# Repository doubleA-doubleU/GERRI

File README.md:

## GERRI (Guidance Enabled Robotic Raceline Interpreter)
#### _Aaron Weatherly_
#### _Northwestern University_

<p>
<br>

<br>
</p>

## Overview
This project allows an off-the-shelf radio controlled car to be converted
into an autonomous vehicle. This is accomplished by replacing the car's 
control system with an Android phone and a PIC32 microcontroller. External
localization is done through HTC vive position sensors. Check out this 
[video][youtube] for a demonstration.

## Required Components 
1. Android phone (I used a Samsung Galaxy S5)
2. Radio Controlled Car (I used a Tamiya TL01)
3. USB OTG cable - micro to mini
4. 3D printed [phone and PCB mounts][parts]
5. Microchip [PIC32MX250F128B][pic] microcontroller in 28-pin SPDIP package
6. VNH5019 [Motor Driver Carrier][hbridge]
7. HTC Vive [Base Station][base]
8. 2x HTC Vive Position Sensor, [TS3633-CM1][vive]
9. Custom [PCB][pcb] with mounting holes for:
	* 28 Pin DIP socket
	* Mini USB connector
	* Slideswitch
	* MCP1702 voltage regulator (TO92)
	* 3mm red LED with 330 Ohm resistor
	* Reset button with 10 kOhm resistor
	* 3mm green LED with 330 Ohm resistor
	* User button with 10 kOhm resistor
	* 8 MHz crystal resonator
	* 4x 0.1 uF capacitors
	* 2x 10 uF polarized capacitors
	* 5-pin breakout for PICkit3 programmer
	* 2x 8-pin breakouts for remaining I/O pins and power/ground connections

## Software
#### In MPLAB X IDE:
1. Create new 32-bit MPLAB Harmony project, named GERRI, for the PIC32MX250F128B
2. Generate code
3. Copy all code from the provided [app.c][appc], [app.h][apph], 
[main.c][main], [default.mhc][default], [system_config.h][config], 
and [system_interrupt.c][interrupt]	into the auto-generated Harmony 
files of same names
4. Install the project onto the PIC
	
#### In Android Studio:
1. Create new project with an Empty Activity, named GERRI
2. Copy the provided [classes.jar][classes] to <your_local_project_path>/GERRI/app/libs/
3. In the IDE, navigate the left panel to Project/GERRI/app/libs/
4. Right click classes.jar, Add as Library, Add to Module: app
5. In the IDE, navigate the left panel to Android/app/res/
6. Right click res, add driectory, name it "xml"
7. Right click xml, add new XML Resource file, name it "device_filter.xml"
8. Open this new xml file and replace the contents with the code from 
the provided [device_filter.xml][filter] file
9. Copy all code from the provided [activity_main.xml][layout], 
[AndroidManifest.xml][manifest], and [MainActivity.java][java] into 
the auto-generated Android Studio files of same name.

## Under the Hood
This is an extension of a much simpler line-following [robot][pathfinder].

#### The Android app:
GERRI begins by using the phone's camera to identify the track ahead. For
me, the track was designated by blue painter's tape, so the key 
lines from `MainActivity.java` are:
```java
for (int startY = 180; startY <= 300; startY = startY + 20) { // which row in the bitmap to analyze to read
    bmp.getPixels(pixels, 0, bmp.getWidth(), 0, startY, bmp.getWidth(), 1);
    // in the row, see if the pixel is blue
    for (int i = 0; i < bmp.getWidth(); i++) {
        if (blue(pixels[i]) > thresh) {
            pixels[i] = rgb(0, 255, 0); // over write the pixel with pure green
            // COM pixel calculation
            M = M + 1;
            sum = sum + i;
        }
    }
    // update the row
    bmp.setPixels(pixels, 0, bmp.getWidth(), 0, startY, bmp.getWidth(), 1);

    // calculate COM for each row
    if (M == 0) {
        COM = 0;
    } else {
        COM = (sum / M) + 1;
        COMavg += COM;
        count++;
    }
}
```
This loop occurs each time there is a new camera frame. We analyze several
rows of pixels, identify which ones are blue, then calculate the average
position for the portion of the track that can be seen. Then, the following
uses a fixed transform from the camera frame to the world frame to determine
where the track is and add that point to a bitmap representing the track:
```java
// average the COMs
if (count == 0) {
    COMavg = 0;
} else {
    COMavg = COMavg / count;
    // calculate a point on the track based on COMavg, xCar, yCar, theta
    float l = (float) (0.025*COMavg); // distance from left of frame to the COM (in cm)
    float d = (float) (Math.sqrt(Math.pow(18.2,2) - Math.pow(l,2))); // distance from the car to the COM (in cm)
    float theta2 = (float) (Math.atan2(8-l,16.35)); // angle from the car to the COM along a line 16.35 cm from car's position (in radians)
    xTrack = (int) (xCar*100 + d*Math.cos(theta + theta2) + 0.5);
    yTrack = (int) (yCar*100 - 200 + d*Math.sin(theta + theta2) +0.5);
    if (lapTime<0.1) {
        xInit = xTrack;
        yInit = yTrack;
    }
    // add that point to the track bitmap
    if (c2 != null) {
		try {
			bmp2.setPixel(xTrack, yTrack, 0xffffffff);
		} catch (Exception e) {}
    }
}
// draw circle at COM
canvas.drawCircle(COMavg, 240, 5, paint1);
// write the COM as text
canvas.drawText("COM = " + COMavg, 10, 30, paint1);
//send COM to PIC
String sendString = String.valueOf(COMavg) + '\n';
try {
    sPort.write(sendString.getBytes(), 1); // 1 is the timeout
} catch (IOException e) {}
```
This process continues until GERRI has completed its first lap and generated
a map of the entire track. It then switches modes from simple line-following 
to a proportional feedback controller that uses the track bitmap as the desired
path. The first step in this phase is to find the nearest point on the track
from the car's current position:
```java
// find nearest white pixel in bmp2 by looking at the rings of pixels around current location
int x = (int) (xCar*100 + 0.5); // convert to cm
int y = (int) (yCar*100 - 200 + 0.5); // convert to cm, shift to fit the bitmap's range
outerLoop:
for (int ring=0; ring<15;ring++) { // looking within 15cm radius
    int[] pixels = new int[2*ring+1];
    for (int row = -ring; row <= ring; row++) {
        try {
            bmp2.getPixels(pixels,0,bmp2.getWidth(),x-ring,y+row,2*ring+1,1);
        } catch (IllegalArgumentException iae) {} // sometimes the data is bad...
        for (int col = -ring; col <= ring; col++) {
            if (pixels[col+ring] == 0xffffffff) {
                // if the pixel is white, define (xDesired,yDesired) as the current row and column of the search
                xDesired = x+col;
                yDesired = y+row;
                if (xDesired_prev == 0) {
                    xDesired_prev = xDesired;
                    yDesired_prev = yDesired;
                }
                // break the both for loops once the track is found
                break outerLoop;
            }
        }
    }
}
```
Next, we calculate the position and angular error as follows:
```java
// calculate position error
posError = (float) Math.sqrt(Math.pow(xDesired - x,2) + Math.pow(yDesired - y,2));

if (posError != 0 && xDesired - xDesired_prev != 0) {
	// calculate desired angle based on current vs previous track points
    thetaDesired = (float) Math.atan2(yDesired - yDesired_prev, xDesired - xDesired_prev);
    if (Math.abs(thetaDesired-thetaDesired_prev) > 0.5) {
        thetaDesired = thetaDesired_prev;
    }
    // calculate angular error
    angError = thetaDesired - theta;
} else {
    if (thetaDesired_prev == 0){
        thetaDesired = theta;
        angError = 0;
    }
    else {
        thetaDesired = thetaDesired_prev;
        angError = thetaDesired - theta;
    }
}
```
Now we have to determine whether the position error should be positive or
negative by determining whether the track is to the left or right of the
car. There is a hard coded assumption here that the track direction is 
always counterclockwise. This was to simplify the if statements below:
```java
// determine whether track is to the left or right (assuming counterclockwise track direction...)
float theta2 = (float) Math.atan2(yDesired - y, xDesired - x); // angle from car to the track
if (thetaDesired >= Math.PI/2 && thetaDesired < Math.PI) {
    if (theta2 >= Math.PI && theta2 < 3*Math.PI/2) { // the track is to the left of the car
        posError = (-1)*posError;
    }
}
else if (thetaDesired >= Math.PI && thetaDesired < 3*Math.PI/2) {
	if (theta2 >= -Math.PI/2 && theta2 < 0) { // the track is to the left of the car
        posError = (-1)*posError;
    }
}
else if (thetaDesired >= -Math.PI/2 && thetaDesired < 0) {
    if (theta2 >=0 && theta2 < Math.PI/2) { // the track is to the left of the car
        posError = (-1)*posError;
    }
}
else if (thetaDesired >= 0 && thetaDesired < Math.PI/2) {
    if (theta2 >= Math.PI/2 && theta2 < Math.PI) { // the track is to the left of the car
        posError = (-1)*posError;
	}
}
```
Finally, we apply the proportional controller based on the [Stanley method][stanley]
from Stanford's entry into the DARPA Grand Challenge.
```java
// use proportional control to calculate a steering angle value between 0 and 640 based on angError (rad) and posError (cm)
// using the Stanley method: http://robots.stanford.edu/papers/thrun.stanley05.pdf
float cmdRad = angError + (float) Math.atan(thresh2*posError/500); // assuming constant velocity, thresh2 is the proportional gain
float cmdDeg = cmdRad*180/((float) Math.PI);
int cmd;
if (cmdDeg <= -30) {
    cmd = 640;
} else if (cmdDeg >= 30) {
	cmd = 1;
} else {
    cmd = (int) (-320*cmdDeg/30 + 320.5);
}
// send steering command to PIC
String sendString = String.valueOf(cmd) + '\n';
try {
    sPort.write(sendString.getBytes(), 1); // 1 is the timeout
} catch (IOException e) {}
```
In both the mapping and controlled cases, the output of the Android app 
is an integer between 0 and 640 that is proportional to desired steering 
angles between positive and negative 30 degrees that is sent to the PIC.

#### The PIC32 firmware:
The PIC32 communicates with the Android app via USB. It takes the integer value
provided by the app and controlls the motor speed/direction and the servo steering 
angle as shown below (from `app.c`):
```c
if (gotRx) { // rxVal should be an int between 0 and 640 (setting motor speed and steering angle from Center of Mass)
    if (rxVal > 640) {          // stop button pressed, no movement, center the steering, reset lap time
        duty = 0;
        LATAbits.LATA1 = 0;
        LATBbits.LATB2 = 1;
        OC3RS = 1000;
        go = 0;
        lapTime = 0.0;
    } else if (rxVal <= 0) {    // reverse direction and previous steering command to find the line again
        duty = 20;
        LATAbits.LATA1 = 1;     // reverse drive motion
        LATBbits.LATB2 = 0;     // reverse drive motion
        rxVal = rxValPrev;
        OC3RS = 680 + rxValPrev;
        go = 1;
    } else {                    // steer towards the COM
        duty = 20;
        LATAbits.LATA1 = 0;     // forward drive motion
        LATBbits.LATB2 = 1;     // forward drive motion
        OC3RS = 1320 - rxVal;   // ranges from 680 to 1320
        go = 1;
    }
	OC1RS = duty*40;            // convert duty cycle based on period register

    rxPos = 0;
    gotRx = 0; // clear the flag
    rxValPrev = rxVal;
    for (j = 0; j < 64; j++) {
        rx[j] = 0; // clear the array
    }
}
```
The PIC32 also provides the position (x,y,theta) as well as the current lap time to the
Android app via USB (also from `app.c`):
```c
// calculate position
x_pos[0] = (LIGHTHOUSEHEIGHT*sin((x_ang[0])*DEG_TO_RAD))/(sin((60+LIGHTHOUSEANGLE-x_ang[0])*DEG_TO_RAD)*sin((120-LIGHTHOUSEANGLE)*DEG_TO_RAD));
y_pos[0] = (2*LIGHTHOUSEHEIGHT*sin(y_ang[0]*DEG_TO_RAD))/sin((150-y_ang[0])*DEG_TO_RAD);
x_pos[1] = (LIGHTHOUSEHEIGHT*sin((x_ang[1])*DEG_TO_RAD))/(sin((60+LIGHTHOUSEANGLE-x_ang[1])*DEG_TO_RAD)*sin((120-LIGHTHOUSEANGLE)*DEG_TO_RAD));
y_pos[1] = (2*LIGHTHOUSEHEIGHT*sin(y_ang[1]*DEG_TO_RAD))/sin((150-y_ang[1])*DEG_TO_RAD);
x = (x_pos[0] + x_pos[1])/2.0;
y = (y_pos[0] + y_pos[1])/2.0;
        
// calculate angle 
if (x_pos[0] == x_pos[1] && y_pos[0] != y_pos[1]) {
	if (y_pos[0] > y_pos[1]) {
        theta = PHI;
    } else {
        theta = PHI + M_PI;
    }
} else if (y_pos[0] == y_pos[1] && x_pos[0] != x_pos[1]) {
    if (x_pos[1] > x_pos[0]){
        theta = PHI + M_PI_2;
    } else {
        theta = PHI + M_PI_2 + M_PI;
    }
} else if (x_pos[0] == x_pos[1] && y_pos[0] == y_pos[1]) {
    theta = 0.0; // should not happen, as sensors are in two different locations, unless sensors are not receiving data
} else {
    theta = atan2(y_pos[1]-y_pos[0],x_pos[1]-x_pos[0]) + PHI + M_PI_2; // always treating left sensor as origin for angle calc
}
            
// calculate lap time
lapTime = lapTime + ((float) (_CP0_GET_COUNT() - startTime)) / 24000000.0;
               
// send data to phone
len = sprintf(dataOut, "%.3f %.3f %.3f %.3f\r\n", x, y, theta, lapTime);
USB_DEVICE_CDC_Write(USB_DEVICE_CDC_INDEX_0,
    &appData.writeTransferHandle, dataOut, len,
    USB_DEVICE_CDC_TRANSFER_FLAGS_DATA_COMPLETE); 
```
The determination of position is done by `system_interrupt.c` through two ISRs,
one for each of the vive sensors. One of the ISRs is below (and the other is very
similar):
```c
void __ISR(_INPUT_CAPTURE_1_VECTOR, IPL5SOFT) IC1ISR(void) {
    static unsigned int ptsL=0;     // previous time stamp for left sensor
    static int stateL = -1;         // state of left sensor
    unsigned int tsL;               // time stamp for left sensor
    int unusedL = IC1BUF;           // the value of timer2 right now, doesn't matter
    unusedL = IC1BUF;               // read multiple times to ensure the buffer is cleared
    unusedL = IC1BUF;               // ...
    unusedL = IC1BUF;               // ...
    LATBbits.LATB13=PORTAbits.RA4;   // match the sensor signal on a debugging pin
    if (PORTAbits.RA4) {            // ignore rising edges
        IFS0bits.IC1IF = 0;         // clear interrupt flag
        return;                     // exit the ISR
    }    
    tsL = _CP0_GET_COUNT();         // get the current time
    if (ptsL > 0) {                 // won't calculate anything the first time through
        unsigned int l = tsL - ptsL;// calculate elapsed time
        if  (l > CYCLE) {           // indicates a synchronization cycle
            stateL = 0;             // prepare to read y angle (from right to left)
        } else {
            if (stateL >= 0) {
                switch (stateL) {   
                    case 0: {
                        y_ang[0]=l*0.0006;  // read y angle in degrees (0 to 120)
                        break;
                    }
                    case 2: {
                        x_ang[0]=l*0.0006;  // read x angle in degrees (0 to 120)
                        break;
                    }
                }
                stateL++;                       // cycle through states
                if (stateL >=4 ) stateL = -1;   // reset state
            }
        }
    }
    ptsL=tsL;           // set the previous time stamp for the next time through
    IFS0bits.IC1IF = 0; // clear the interrupt flag
}
```
This works because the base station conducts two infrared sweeps, one horizontal and one
vertical. By timing the pulses seen by the sensors, we can determine the angle at which the
base station "sees" the sensor in both directions. With some basic trigonometry, this can
be converted into meters. By doing this with two sensors, the car's heading can also be
determined, as seen above. 

## Future Work
Although this method allows for some autonomous features, it would be ideal to utilize the
track map that is generated to do some more detailed path planning. This could allow for 
the calculation of a racing line that is optimized to decrease the radius of curvature of 
the path and hence the required steering effort of the car.

I also considered including an accelerometer in order to detect loss of traction and 
adjust motor speed accordingly. Due to the limitations on track size based on my workspace,
I decided to use a fixed (and relatively slow) velocity. If the track size were larger,
it would be possible to modulate velocity based on the current error and speed up or slow
down based on the curvature of the track. In that scenario, an accelerometer would be quite 
useful.

[youtube]: https://youtu.be/dq8rHDOIuIY
[parts]: https://github.com/weatherman03/GERRI/tree/master/Parts
[pic]: http://www.microchipdirect.com/product/PIC32MX250F128B
[hbridge]: https://www.pololu.com/product/1451
[base]: https://www.vive.com/us/accessory/base-station/
[vive]: https://www.triadsemi.com/product/ts3633-cm1/
[pcb]: https://github.com/weatherman03/GERRI/tree/master/Eagle
[appc]: https://github.com/weatherman03/GERRI/blob/master/Harmony/app.c
[apph]: https://github.com/weatherman03/GERRI/blob/master/Harmony/app.h
[main]: https://github.com/weatherman03/GERRI/blob/master/Harmony/main.c
[default]: https://github.com/weatherman03/GERRI/blob/master/Harmony/default.mhc
[config]: https://github.com/weatherman03/GERRI/blob/master/Harmony/system_config.h
[interrupt]: https://github.com/weatherman03/GERRI/blob/master/Harmony/system_interrupt.c
[classes]: https://github.com/weatherman03/GERRI/blob/master/Android/classes.jar
[filter]: https://github.com/weatherman03/GERRI/blob/master/Android/device_filter.xml
[layout]: https://github.com/weatherman03/GERRI/blob/master/Android/activity_main.xml
[manifest]: https://github.com/weatherman03/GERRI/blob/master/Android/AndroidManifest.xml
[java]: https://github.com/weatherman03/GERRI/blob/master/Android/MainActivity.java
[pathfinder]: https://github.com/weatherman03/PathFinder
[stanley]: http://robots.stanford.edu/papers/thrun.stanley05.pdf

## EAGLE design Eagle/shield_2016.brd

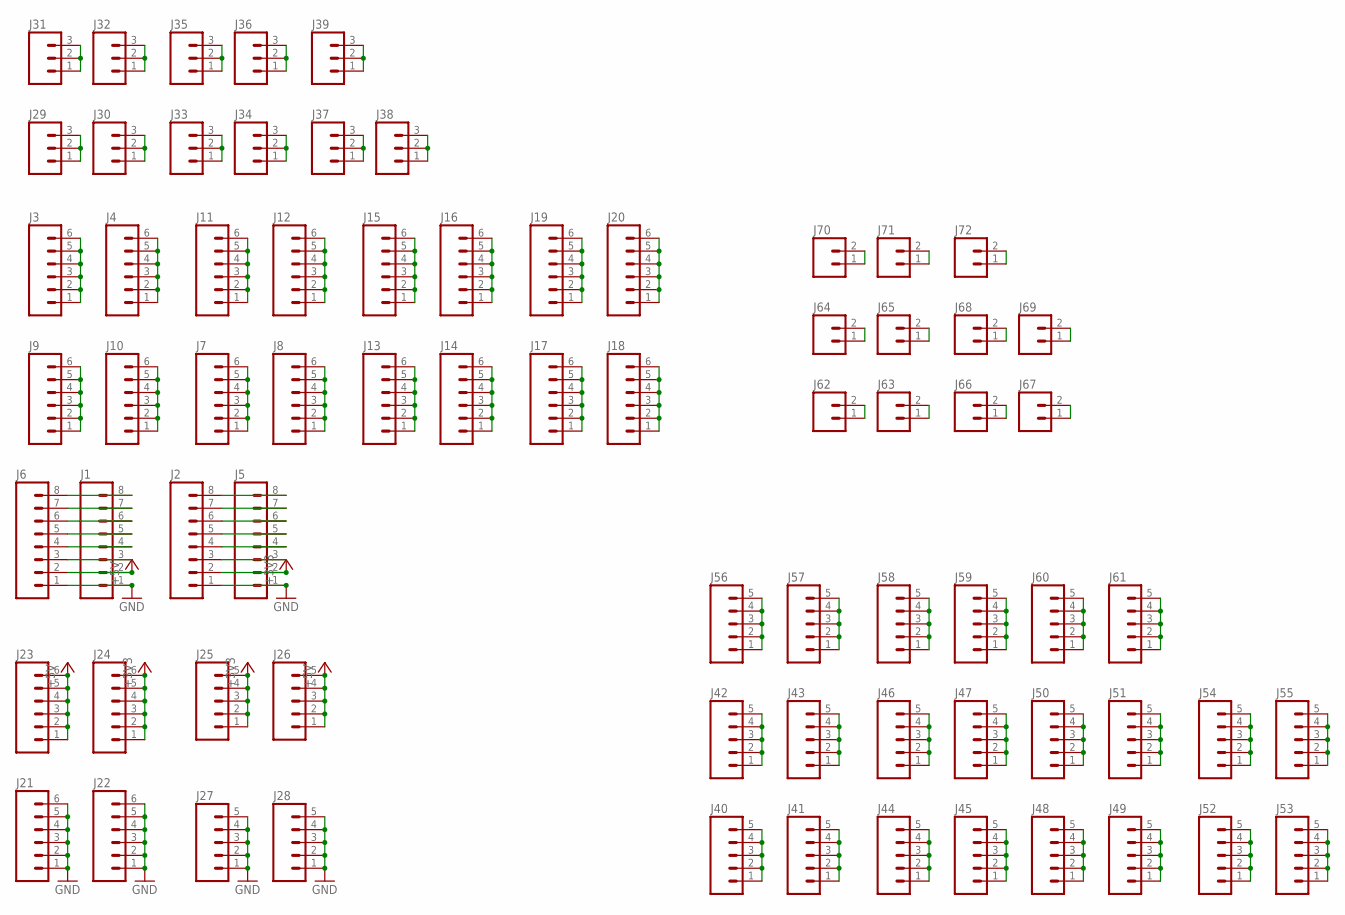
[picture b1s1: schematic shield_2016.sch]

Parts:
J1, J2, J5, J6: M08; 1X08_ROUND
J3, J4, J7, J8, J9, J10, J11, J12, J13, J14, J15, J16, J17, J18, J19, J20, J21, J22, J23, J24: M06SILK_FEMALE_PTH; 1X06
J25, J26, J27, J28, J40, J41, J42, J43, J44, J45, J46, J47, J48, J49, J50, J51, J52, J53, J54, J55, J56, J57, J58, J59, J60, J61: M05PTH; 1X05
J29, J30, J31, J32, J33, J34, J35, J36, J37, J38, J39: M03PTH; 1X03
J62, J63, J64, J65, J66, J67, J68, J69, J70, J71, J72: M02PTH; 1X02

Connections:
+3V3: J2.2, J5.2, J24.1, J24.2, J24.3, J24.4, J24.5, J24.6, J25.1, J25.2, J25.3, J25.4, J25.5
+5V: J1.2, J6.2, J23.1, J23.2, J23.3, J23.4, J23.5, J23.6, J26.1, J26.2, J26.3, J26.4, J26.5
GND: J1.1, J2.1, J5.1, J6.1, J21.1, J21.2, J21.3, J21.4, J21.5, J21.6, J22.1, J22.2, J22.3, J22.4, J22.5, J22.6, J27.1, J27.2, J27.3, J27.4, J27.5, J28.1, J28.2, J28.3, J28.4, J28.5
unnamed: J3.1, J3.2, J3.3, J3.4, J3.5, J3.6
unnamed: J4.1, J4.2, J4.3, J4.4, J4.5, J4.6
unnamed: J29.1, J29.2, J29.3
unnamed: J30.1, J30.2, J30.3
unnamed: J1.3, J6.3
unnamed: J1.4, J6.4
unnamed: J1.5, J6.5
unnamed: J1.6, J6.6
unnamed: J1.7, J6.7
unnamed: J1.8, J6.8
unnamed: J31.1, J31.2, J31.3
unnamed: J32.1, J32.2, J32.3
unnamed: J2.3, J5.3
unnamed: J2.4, J5.4
unnamed: J2.5, J5.5
unnamed: J2.6, J5.6
unnamed: J2.7, J5.7
unnamed: J2.8, J5.8
unnamed: J7.1, J7.2, J7.3, J7.4, J7.5, J7.6
unnamed: J8.1, J8.2, J8.3, J8.4, J8.5, J8.6
unnamed: J9.1, J9.2, J9.3, J9.4, J9.5, J9.6
unnamed: J10.1, J10.2, J10.3, J10.4, J10.5, J10.6
unnamed: J11.1, J11.2, J11.3, J11.4, J11.5, J11.6
unnamed: J12.1, J12.2, J12.3, J12.4, J12.5, J12.6
unnamed: J13.1, J13.2, J13.3, J13.4, J13.5, J13.6
unnamed: J14.1, J14.2, J14.3, J14.4, J14.5, J14.6
unnamed: J15.1, J15.2, J15.3, J15.4, J15.5, J15.6
unnamed: J16.1, J16.2, J16.3, J16.4, J16.5, J16.6
unnamed: J17.1, J17.2, J17.3, J17.4, J17.5, J17.6
unnamed: J18.1, J18.2, J18.3, J18.4, J18.5, J18.6
unnamed: J19.1, J19.2, J19.3, J19.4, J19.5, J19.6
unnamed: J20.1, J20.2, J20.3, J20.4, J20.5, J20.6
unnamed: J33.1, J33.2, J33.3
unnamed: J34.1, J34.2, J34.3
unnamed: J35.1, J35.2, J35.3
unnamed: J36.1, J36.2, J36.3
unnamed: J37.1, J37.2, J37.3
unnamed: J38.1, J38.2, J38.3
unnamed: J39.1, J39.2, J39.3
unnamed: J40.1, J40.2, J40.3, J40.4, J40.5
unnamed: J41.1, J41.2, J41.3, J41.4, J41.5
unnamed: J42.1, J42.2, J42.3, J42.4, J42.5
unnamed: J43.1, J43.2, J43.3, J43.4, J43.5
unnamed: J44.1, J44.2, J44.3, J44.4, J44.5
unnamed: J45.1, J45.2, J45.3, J45.4, J45.5
unnamed: J46.1, J46.2, J46.3, J46.4, J46.5
unnamed: J47.1, J47.2, J47.3, J47.4, J47.5
unnamed: J48.1, J48.2, J48.3, J48.4, J48.5
unnamed: J49.1, J49.2, J49.3, J49.4, J49.5
unnamed: J50.1, J50.2, J50.3, J50.4, J50.5
unnamed: J51.1, J51.2, J51.3, J51.4, J51.5
unnamed: J52.1, J52.2, J52.3, J52.4, J52.5
unnamed: J53.1, J53.2, J53.3, J53.4, J53.5
unnamed: J54.1, J54.2, J54.3, J54.4, J54.5
unnamed: J55.1, J55.2, J55.3, J55.4, J55.5
unnamed: J56.1, J56.2, J56.3, J56.4, J56.5
unnamed: J57.1, J57.2, J57.3, J57.4, J57.5
unnamed: J58.1, J58.2, J58.3, J58.4, J58.5
unnamed: J59.1, J59.2, J59.3, J59.4, J59.5
unnamed: J60.1, J60.2, J60.3, J60.4, J60.5
unnamed: J61.1, J61.2, J61.3, J61.4, J61.5
unnamed: J62.1, J62.2
unnamed: J63.1, J63.2
unnamed: J64.1, J64.2
unnamed: J65.1, J65.2
unnamed: J66.1, J66.2
unnamed: J67.1, J67.2
unnamed: J68.1, J68.2
unnamed: J69.1, J69.2
unnamed: J70.1, J70.2
unnamed: J71.1, J71.2
unnamed: J72.1, J72.2

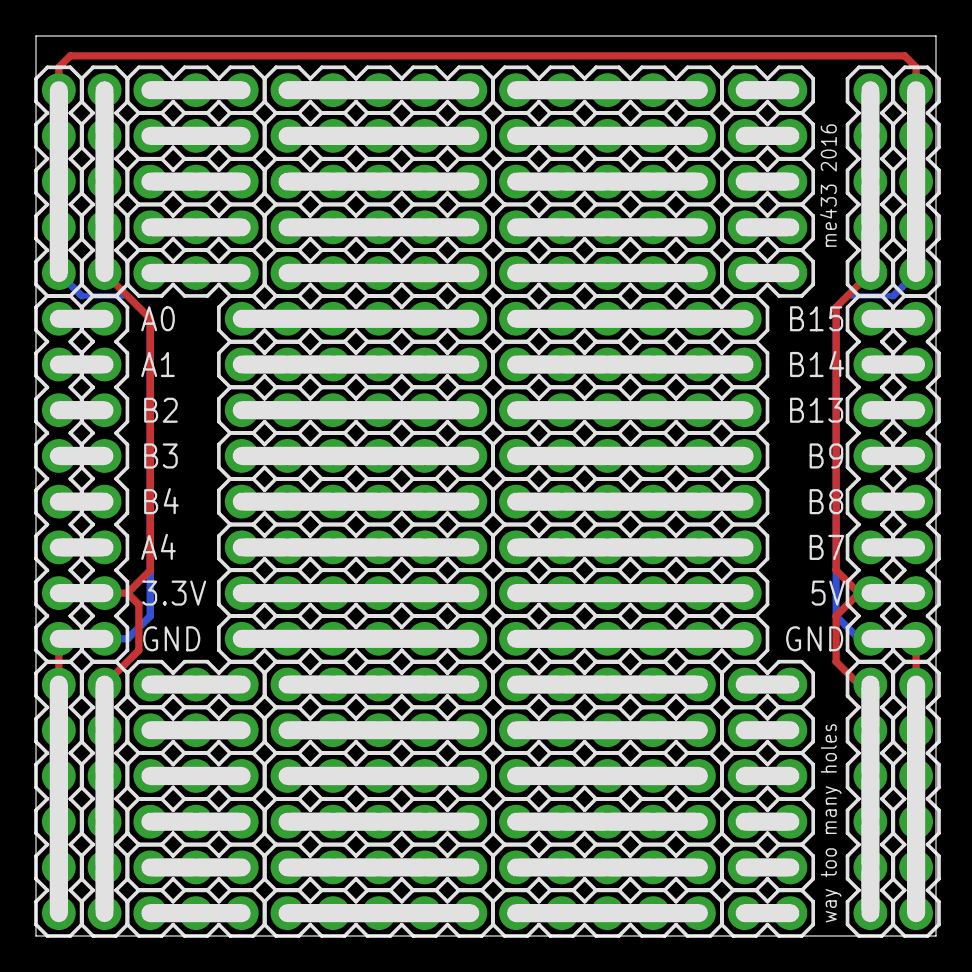
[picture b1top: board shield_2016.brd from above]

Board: 2 copper layers, 50.0 x 50.0 mm, 72 parts (0 on the bottom side), 75 nets.

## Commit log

2017-07-20 :boom::camel: Added .gitattributes & .gitignore files
2017-07-20 readme
2017-07-20 References
2017-09-17 TL01 Files
2017-10-26 Added some parts and reference material
2017-10-27 Vive sensors implemented, basic line-following behavior
2017-11-08 Mapping of track data complete
2017-11-08 fixed x,y discrepency in vive calculation, recalibrated for new servo, changed backup behavior for line following
2017-12-03 Proportional steering control implemented
2017-12-03 Added PCB shield files
2017-12-06 Final Android code, converting README to markdown
2017-12-06 Updated README, still need link to video
2017-12-07 Updated README, link to demo video is included

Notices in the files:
parts and their libraries:
SparkFun-Connectors: Licensing: Creative Commons ShareAlike 4.0 International - https://creativecommons.org/licenses/by-sa/4.0
